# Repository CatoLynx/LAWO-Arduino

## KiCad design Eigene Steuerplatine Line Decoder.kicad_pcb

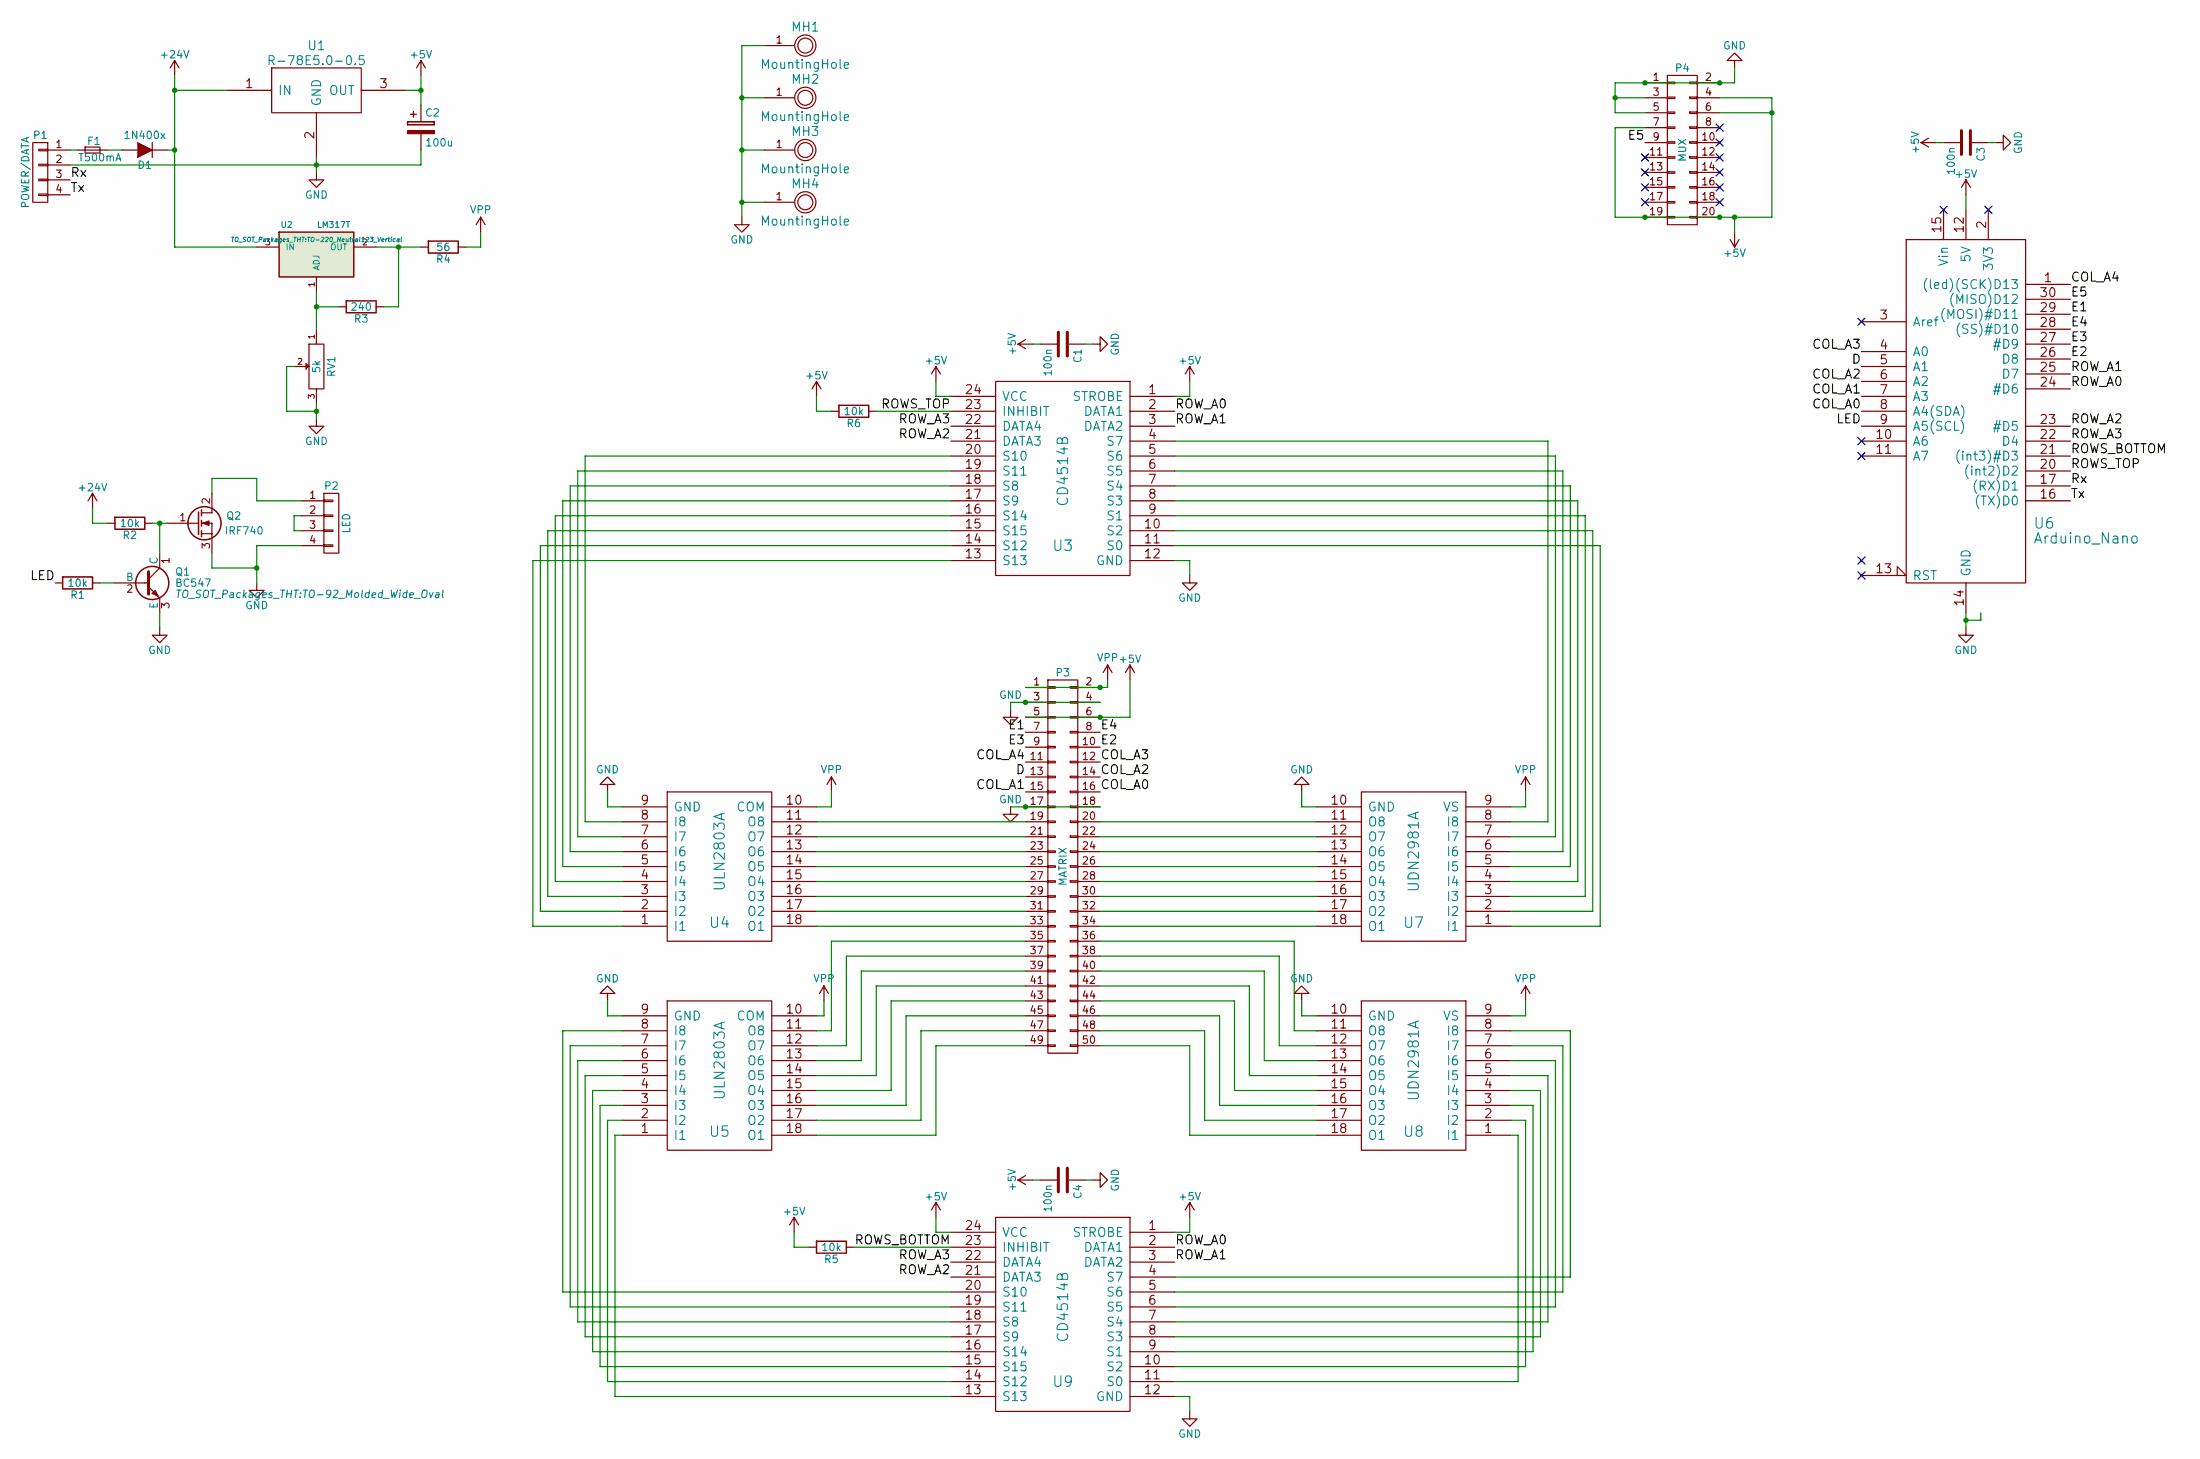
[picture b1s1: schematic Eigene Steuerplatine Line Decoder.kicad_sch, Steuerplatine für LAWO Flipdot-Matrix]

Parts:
C1, C3, C4: 100n; C_Rect_L7_W2.5_P5
C2: 100u; C_Radial_D5_L11_P2.5
D1: 1N400x; Diode_DO-35_SOD27_Horizontal_RM10
F1: T500mA; Fuseholder5x20_horiz_open_Schurter_0031_8201
MH1, MH2, MH3, MH4: MountingHole; 1pin
P1: POWER/DATA; Terminal_Conn_4pin_RM5.08
P2: LED; Terminal_Conn_4pin_RM5.08
P3: MATRIX; IDC_Header_Straight_50pins
P4: MUX; IDC_Header_Straight_20pins
Q1: BC547; TO-92_Molded_Wide_Oval
Q2: IRF740; TO-220_Neutral123_Vertical
R1, R2, R5, R6: 10k; Resistor_Horizontal_RM10mm
R3: 240; Resistor_Horizontal_RM10mm
R4: 56; Resistor_Horizontal_RM20mm
RV1: 5k; Potentiometer_Bourns_3296Y_3-8Zoll_Angular_ScrewUp
U1: R-78E5.0-0.5; DC_DC_Converter_W11.5_L8.5_P2.54
U2: LM317T; TO-220_Neutral123_Vertical
U3, U9: CD4514B; DIP-24_W15.24mm_LongPads
U4, U5: ULN2803A; DIP-18_W7.62mm_LongPads
U6: Arduino_Nano
U7, U8: UDN2981A; DIP-18_W7.62mm_LongPads

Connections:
+5V: C1.2, C2.1, C3.2, C4.2, P3.5, P3.6, P4.4, P4.6, P4.7, P4.19, P4.20, R5.2, R6.2, U1.3 (OUT), U3.1 (STROBE), U3.24 (VCC), U6.12 (5V), U9.1 (STROBE), U9.24 (VCC)
+24V: D1.1 (K), D1.2 (A), F1.2, R2.2, U1.1 (IN), U2.3 (IN)
/COL_A0: P3.16, U6.8 (A4(SDA))
/COL_A1: P3.15, U6.7 (A3)
/COL_A2: P3.14, U6.6 (A2)
/COL_A3: P3.12, U6.4 (A0)
/COL_A4: P3.11, U6.1 ((led)(SCK)D13)
/D: P3.13, U6.5 (A1)
/E1: P3.7, U6.29 ((MOSI)#D11)
/E2: P3.10, U6.26 (D8)
/E3: P3.9, U6.27 (#D9)
/E4: P3.8, U6.28 ((SS)#D10)
/E5: P4.9, U6.30 ((MISO)D12)
/LED: R1.2, U6.9 (A5(SCL))
/ROWS_BOTTOM: R5.1, U6.21 ((int3)#D3), U9.23 (INHIBIT)
/ROWS_TOP: R6.1, U3.23 (INHIBIT), U6.20 ((int2)D2)
/ROW_A0: U3.2 (DATA1), U6.24 (#D6), U9.2 (DATA1)
/ROW_A1: U3.3 (DATA2), U6.25 (D7), U9.3 (DATA2)
/ROW_A2: U3.21 (DATA3), U6.23 (#D5), U9.21 (DATA3)
/ROW_A3: U3.22 (DATA4), U6.22 (D4), U9.22 (DATA4)
/Rx: P1.3, U6.17 ((RX)D1)
/Tx: P1.4, U6.16 ((TX)D0)
GND: C1.1, C2.2, C3.1, C4.1, MH1.1, MH2.1, MH3.1, MH4.1, P1.2, P2.4, P3.3, P3.4, P3.17, P3.18, P4.1, P4.2, P4.3, P4.5, Q1.3 (E), Q2.3 (S), RV1.2, RV1.3, U1.2 (GND), U3.12 (GND), U4.9 (GND), U5.9 (GND), U6.14 (GND), U6.19 (GND), U7.10 (GND), U8.10 (GND), U9.12 (GND)
unnamed: F1.1, P1.1
unnamed: P2.1, Q2.2 (D)
unnamed: P2.2, P2.3
unnamed: P3.19, U4.11 (O8)
unnamed: P3.20, U7.11 (O8)
unnamed: P3.21, U4.12 (O7)
unnamed: P3.22, U7.12 (O7)
unnamed: P3.23, U4.13 (O6)
unnamed: P3.24, U7.13 (O6)
unnamed: P3.25, U4.14 (O5)
unnamed: P3.26, U7.14 (O5)
unnamed: P3.27, U4.15 (O4)
unnamed: P3.28, U7.15 (O4)
unnamed: P3.29, U4.16 (O3)
unnamed: P3.30, U7.16 (O3)
unnamed: P3.31, U4.17 (O2)
unnamed: P3.32, U7.17 (O2)
unnamed: P3.33, U4.18 (O1)
unnamed: P3.34, U7.18 (O1)
unnamed: P3.35, U5.11 (O8)
unnamed: P3.36, U8.11 (O8)
unnamed: P3.37, U5.12 (O7)
unnamed: P3.38, U8.12 (O7)
unnamed: P3.39, U5.13 (O6)
unnamed: P3.40, U8.13 (O6)
unnamed: P3.41, U5.14 (O5)
unnamed: P3.42, U8.14 (O5)
unnamed: P3.43, U5.15 (O4)
unnamed: P3.44, U8.15 (O4)
unnamed: P3.45, U5.16 (O3)
unnamed: P3.46, U8.16 (O3)
unnamed: P3.47, U5.17 (O2)
unnamed: P3.48, U8.17 (O2)
unnamed: P3.49, U5.18 (O1)
unnamed: P3.50, U8.18 (O1)
unnamed: Q1.1 (C), Q2.1 (G), R2.1
unnamed: Q1.2 (B), R1.1
unnamed: R3.1, R4.2, U2.2 (OUT)
unnamed: R3.2, RV1.1, U2.1 (ADJ)
unnamed: U3.4 (S7), U7.8 (I8)
unnamed: U3.5 (S6), U7.7 (I7)
unnamed: U3.6 (S5), U7.6 (I6)
unnamed: U3.7 (S4), U7.5 (I5)
unnamed: U3.8 (S3), U7.4 (I4)
unnamed: U3.9 (S1), U7.3 (I3)
unnamed: U3.10 (S2), U7.2 (I2)
unnamed: U3.11 (S0), U7.1 (I1)
unnamed: U3.13 (S13), U4.1 (I1)
unnamed: U3.14 (S12), U4.2 (I2)
unnamed: U3.15 (S15), U4.3 (I3)
unnamed: U3.16 (S14), U4.4 (I4)
unnamed: U3.17 (S9), U4.5 (I5)
unnamed: U3.18 (S8), U4.6 (I6)
unnamed: U3.19 (S11), U4.7 (I7)
unnamed: U3.20 (S10), U4.8 (I8)
unnamed: U5.1 (I1), U9.13 (S13)
unnamed: U5.2 (I2), U9.14 (S12)
unnamed: U5.3 (I3), U9.15 (S15)
unnamed: U5.4 (I4), U9.16 (S14)
unnamed: U5.5 (I5), U9.17 (S9)
unnamed: U5.6 (I6), U9.18 (S8)
unnamed: U5.7 (I7), U9.19 (S11)
unnamed: U5.8 (I8), U9.20 (S10)
unnamed: U8.1 (I1), U9.11 (S0)
unnamed: U8.2 (I2), U9.10 (S2)
unnamed: U8.3 (I3), U9.9 (S1)
unnamed: U8.4 (I4), U9.8 (S3)
unnamed: U8.5 (I5), U9.7 (S4)
unnamed: U8.6 (I6), U9.6 (S5)
unnamed: U8.7 (I7), U9.5 (S6)
unnamed: U8.8 (I8), U9.4 (S7)
VPP: P3.1, P3.2, R4.1, U4.10 (COM), U5.10 (COM), U7.9 (VS), U8.9 (VS)

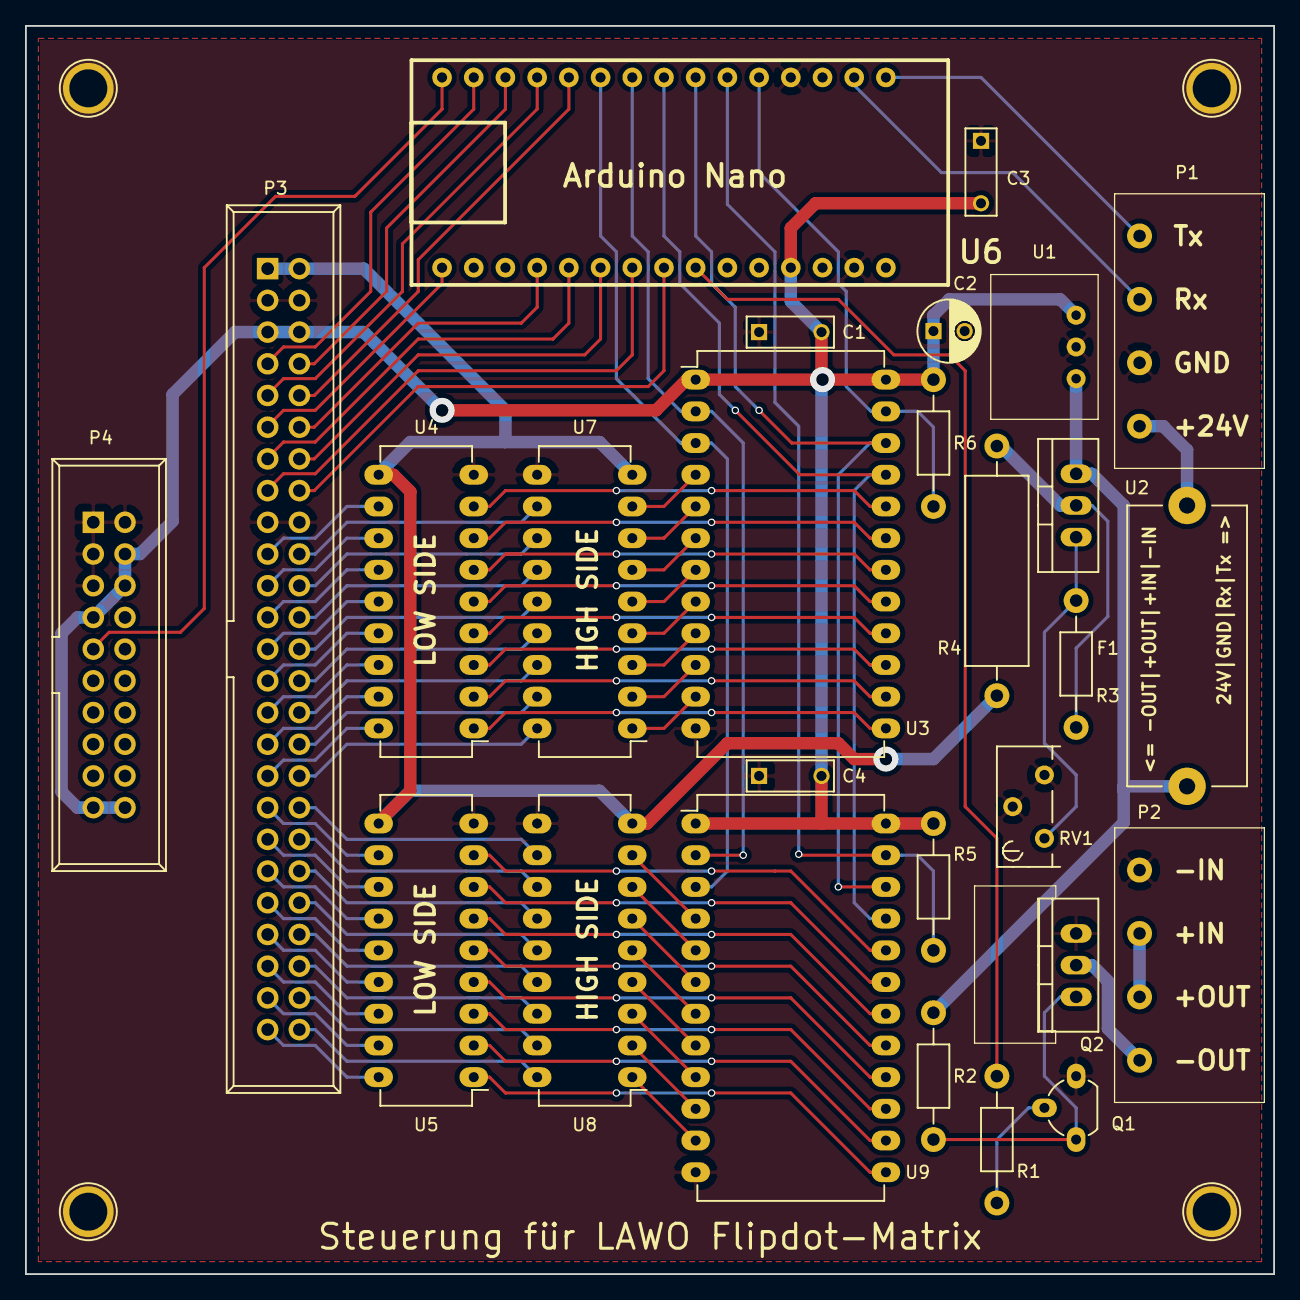
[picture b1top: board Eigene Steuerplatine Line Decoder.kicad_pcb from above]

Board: 2 copper layers, 100.0 x 100.0 mm, 31 parts (0 on the bottom side), 95 nets.

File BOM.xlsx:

Item | Qty | Reference(s) | Value | Order No. / URL | Supplier
1.0 | 3.0 | C3,C1,C4 | 100n | X7R-5 100N | reichelt
2.0 | 1.0 | C2 | 100u | RAD 100/25 | reichelt
3.0 | 1.0 | F1 | T500mA | RND 170-00041 | reichelt
4.0 | 1.0 | P1,P2 | POWER/DATA,LED | AKL 230-04 + AKL 249-04 | reichelt
5.0 | 1.0 | P3 | MATRIX | WSL 50G | reichelt
6.0 | 1.0 | P4 | MUX | WSL 20G | reichelt
7.0 | 1.0 | Q1 | BC547 | BC 547C | reichelt
8.0 | 1.0 | Q2 | IRF740 | IRF 740 | reichelt
9.0 | 4.0 | R5,R6,R1,R2 | 10k | 1/4W 10K | reichelt
10.0 | 1.0 | R3 | 240 | 1/4W 240 | reichelt
11.0 | 1.0 | R4 | 56 | 2W METALL 56 | reichelt
12.0 | 1.0 | RV1 | 5k | 64Y-5,0K | reichelt
13.0 | 1.0 | U1 | R-78E5.0-0.5 | R-78E50-05 | reichelt
14.0 | 1.0 | U2 | LM317T | LM 317-220 | reichelt
15.0 | 2.0 | U9,U3 | CD4514B | https://www.ebay.de/itm/110545119205 | eBay
16.0 | 2.0 | U5,U4 | ULN2803A | ULN 2803A | reichelt
17.0 | 1.0 | U6 | Arduino_Nano | https://www.ebay.de/itm/252742123829 | eBay
18.0 | 2.0 | U7,U8 | UDN2981A | UDN 2981 | reichelt
19.0 | 4.0 | U4,U5,U7,U8 | Sockel | GS 18 | reichelt
20.0 | 2.0 | U3,U9 | Sockel | GS 24 | reichelt
21.0 | 2.0 | U6 | Sockel | https://www.ebay.de/itm/172461135540 | eBay
22.0 | 1.0 | Q2 | Kühlkörper | 188158 | Conrad

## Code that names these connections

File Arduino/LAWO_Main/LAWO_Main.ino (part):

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 * PIN DECLARATIONS
 */

#define ROW_A0 6
#define ROW_A1 7
#define ROW_A2 5
#define ROW_A3 4
#define COL_A0 A4
#define COL_A1 A3
#define COL_A2 A2
#define COL_A3 A0
#define COL_A4 13
#define ROWS_BOTTOM 3
#define ROWS_TOP 2
#define D A1
#define E1 11
#define E2 8
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  digitalWrite(ROWS_BOTTOM, HIGH);
  digitalWrite(ROWS_TOP, HIGH);

  pinMode(ROW_A0, OUTPUT);
  pinMode(ROW_A1, OUTPUT);
  pinMode(ROW_A2, OUTPUT);
  pinMode(ROW_A3, OUTPUT);
  pinMode(COL_A0, OUTPUT);
  pinMode(COL_A1, OUTPUT);
  pinMode(COL_A2, OUTPUT);
  pinMode(COL_A3, OUTPUT);
  pinMode(COL_A4, OUTPUT);
  pinMode(ROWS_BOTTOM, OUTPUT);
  pinMode(ROWS_TOP, OUTPUT);
  pinMode(D, OUTPUT);
  pinMode(E1, OUTPUT);
  pinMode(E2, OUTPUT);
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
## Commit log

2020-04-20 Initial version
2023-11-21 Convert to KiCad 7 project

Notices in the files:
Arduino/LAWO_Main/LAWO_Main.ino:
Copyright (C) 2016 Julian Metzler
This program is free software: you can redistribute it and/or modify
it under the terms of the GNU Affero General Public License as published by
the Free Software Foundation, either version 3 of the License, or
(at your option) any later version.
